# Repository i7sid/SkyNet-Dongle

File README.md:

SkyNet-Dongle
=============

Welcome to the SkyNet-Dongle git repository!
The initial work was done in the context of a bachelor thesis at the
Friedrich-Alexander University Erlangen-Nürnberg.
Some updates were made during a master thesis at the
Friedrich-Alexander University Erlangen-Nürnberg.

Hardware
--------
The main components are
* CPU: LPC1769
* Radio: [LoRa-Feather](https://learn.adafruit.com/adafruit-feather-m0-radio-with-lora-radio-module?view=all)

Firmware
--------
The firmware for the LPC1769 is written entirely in C99 and can **basically**
be compiled by a standard GNU GCC cross compiling toolchain.
Currently an Eclipse project is shipped that works with
[LPCXpresso](https://www.lpcware.com/lpcxpresso/download).
Additionally you need the [LPCOpen chip library](http://www.lpcware.com/lpcopen).

If both projects - lpc_chip_175x_6x and SkyNet-Dongle-Firmware - are present in
your current workspace you should be able to successfully compile the firmware.

The firmware uses the Si446x API library from Silicon Laboratories, Inc.
The library was slightly adjusted to compile for and work nicely on LPC1769.

Pinouts
-------
... are documented in `board/pinouts.txt`.

Flashing / Programming
----------------------
First flashing has to be done via ISP or JTAG.
Flash `bootloader/src/bootloader.bin` to the processor.
Afterwards you should be able to flash new firmware files
(.bin) via USB and mass storage emulation.

That works as following:
Send via USB CDC serial terminal a "goto bootloader" command.
You can use:

    ./usb-host/skynet-usb-host

(You have to compile the host application before that.)

The dongle restarts and goes into bootloader mode.
Now the dongle is detected by host as a mass storage device.
Copy firmware binary to the mass storage device and *eject the device* afterwards:

    sudo eject /dev/{devices name, usually sdb, sdc, sdd, or any...}

or:

    sudo umount {MOUNTPOINT}
    sudo udisk --detach /dev/{devices name, usually sdb, sdc, sdd, or any...}

Bootloader source: https://github.com/openxc/openlpc-USB_Bootloader

EAGLE files (schematics, layout)
--------------------------------

The eagle files contained in this repository
(schematics, layouts) use the following libraries:
* LPC1769: [lpc1xxx-v6.lbr](http://www.cadsoft.de/downloads/file/lpc1xxx-v6.lbr)
* HC-05: [Bluetooth HC-05.lbr](https://github.com/ErichStyger/mcuoneclipse/tree/master/Eagle/Library)
* MCP73871: [microchip-battery.lbr](https://github.com/scott-42/eagle-lib)
* Micro USB connector: [usb_con-update.lbr](http://www.cadsoft.de/downloads/file/usb_con-update.lbr)
* Switch: [switch-ck.lbr](https://github.com/robertstarr/lbr_user/blob/master/switch-ck.lbr)
* [Microbuilder Library](http://www.microbuilder.eu/Projects/EagleFootprintLibrary.aspx)
* RF4463PRO (from this repository)
* skynet_other (from this repository)

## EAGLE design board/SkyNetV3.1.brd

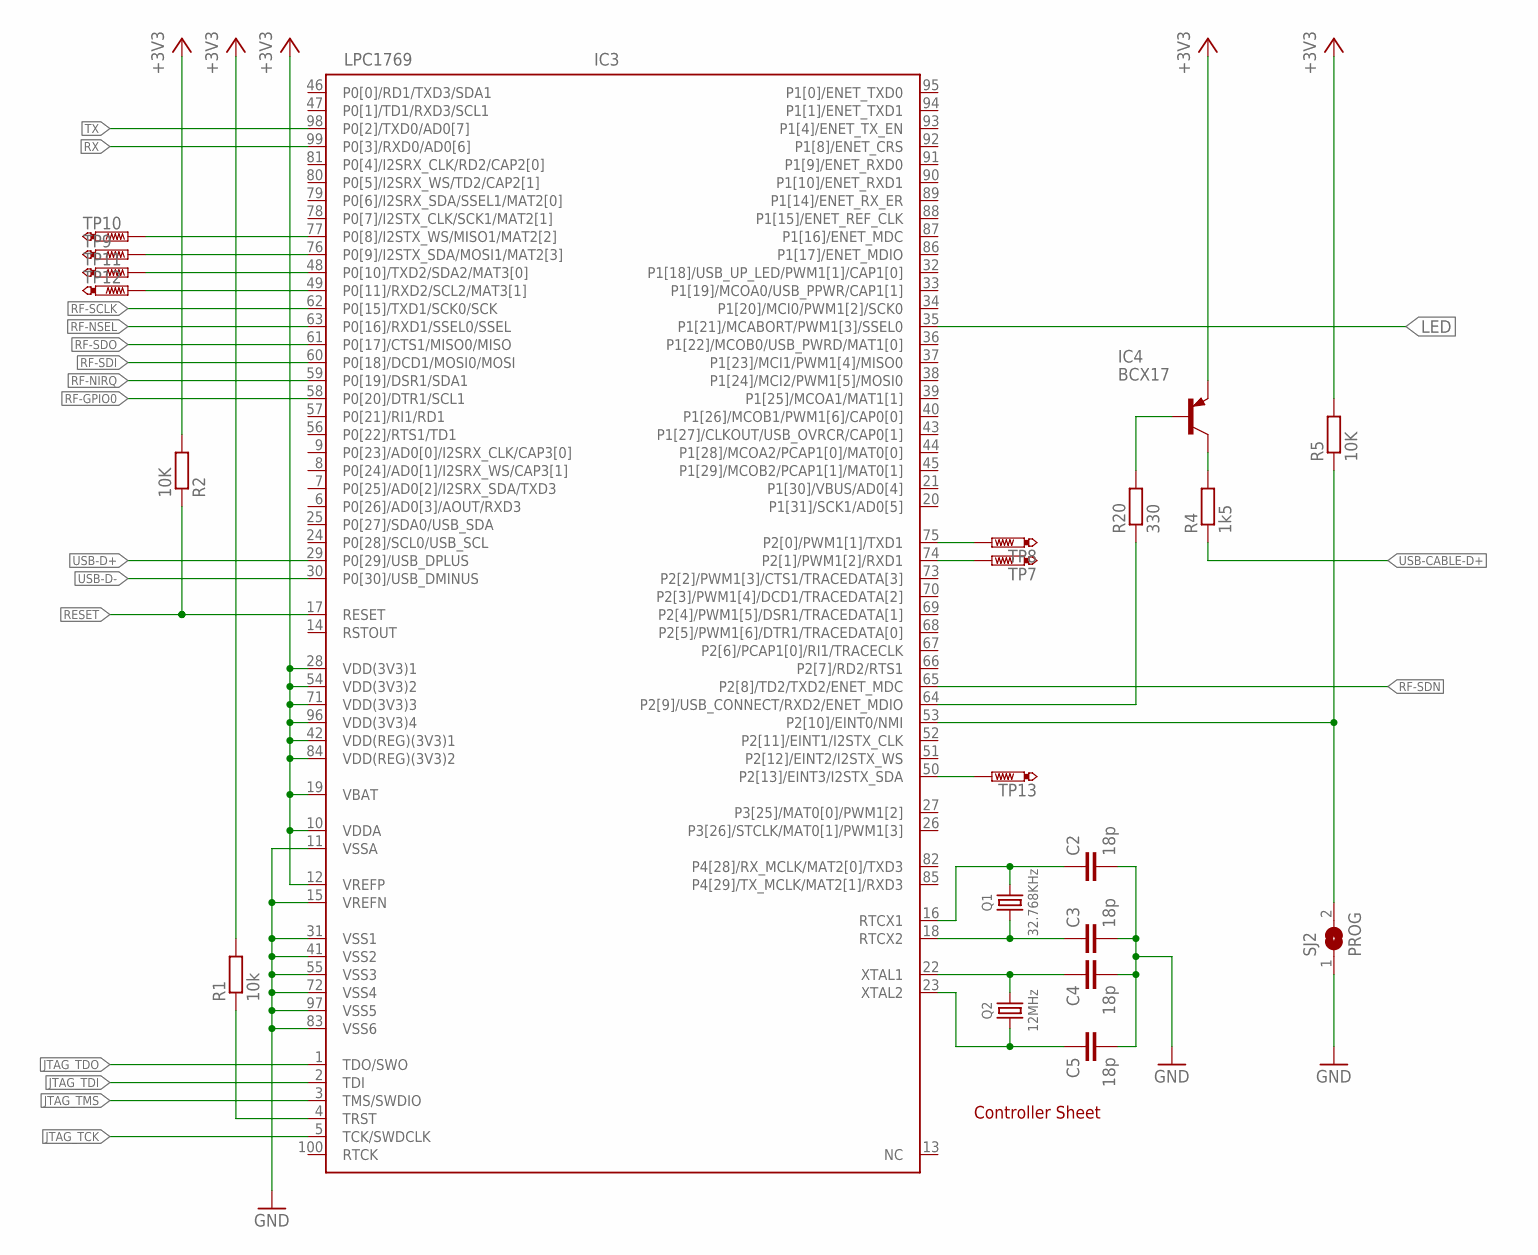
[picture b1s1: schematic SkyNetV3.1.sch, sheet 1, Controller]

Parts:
C2, C3, C4, C5: 18p; C0603
IC3: LPC1769; LQFP100-14X14
IC4: BCX17; SOT23
Q1: 32.768KHz; XTAL_49_18
Q2: 12MHz; XTAL_50_32
R1: 10k; R0603
R2, R5: 10K; R0603
R4: 1k5; R0603
R20: 330; R0603
SJ2: PROG; SJ
TP7, TP8, TP9, TP10, TP11, TP12, TP13: PTR1B1,27; B1,27

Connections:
+3V3: IC3.10 (VDDA), IC3.12 (VREFP), IC3.19 (VBAT), IC3.28 (VDD(3V3)1), IC3.42 (VDD(REG)(3V3)1), IC3.54 (VDD(3V3)2), IC3.71 (VDD(3V3)3), IC3.84 (VDD(REG)(3V3)2), IC3.96 (VDD(3V3)4), IC4.2 (E), R1.2, R2.2, R5.2; also elsewhere on the board
GND: C2.2, C3.2, C4.2, C5.2, IC3.11 (VSSA), IC3.15 (VREFN), IC3.31 (VSS1), IC3.41 (VSS2), IC3.55 (VSS3), IC3.72 (VSS4), IC3.83 (VSS6), IC3.97 (VSS5), SJ2.1; also elsewhere on the board
JTAG-TRST: IC3.4 (TRST), R1.1
JTAG_TCK: IC3.5 (TCK/SWDCLK); also elsewhere on the board
JTAG_TDI: IC3.2 (TDI); also elsewhere on the board
JTAG_TDO: IC3.1 (TDO/SWO); also elsewhere on the board
JTAG_TMS: IC3.3 (TMS/SWDIO); also elsewhere on the board
LED: IC3.35 (P1[21]/MCABORT/PWM1[3]/SSEL0); also elsewhere on the board
unnamed: IC3.75 (P2[0]/PWM1[1]/TXD1), TP8.TP
unnamed: IC3.76 (P0[9]/I2STX_SDA/MOSI1/MAT2[3]), TP9.TP
unnamed: IC3.77 (P0[8]/I2STX_WS/MISO1/MAT2[2]), TP10.TP
unnamed: IC3.74 (P2[1]/PWM1[2]/RXD1), TP7.TP
unnamed: IC3.49 (P0[11]/RXD2/SCL2/MAT3[1]), TP12.TP
unnamed: IC3.48 (P0[10]/TXD2/SDA2/MAT3[0]), TP11.TP
unnamed: IC3.50 (P2[13]/EINT3/I2STX_SDA), TP13.TP
PROG: IC3.53 (P2[10]/EINT0/NMI), R5.1, SJ2.2
RESET: IC3.17 (RESET), R2.1; also elsewhere on the board
RF-GPIO0: IC3.58 (P0[20]/DTR1/SCL1); also elsewhere on the board
RF-NIRQ: IC3.59 (P0[19]/DSR1/SDA1); also elsewhere on the board
RF-NSEL: IC3.63 (P0[16]/RXD1/SSEL0/SSEL); also elsewhere on the board
RF-SCLK: IC3.62 (P0[15]/TXD1/SCK0/SCK); also elsewhere on the board
RF-SDI: IC3.60 (P0[18]/DCD1/MOSI0/MOSI); also elsewhere on the board
RF-SDN: IC3.65 (P2[8]/TD2/TXD2/ENET_MDC); also elsewhere on the board
RF-SDO: IC3.61 (P0[17]/CTS1/MISO0/MISO); also elsewhere on the board
RTCX1: C2.1, IC3.16 (RTCX1), Q1.2
RTCX2: C3.1, IC3.18 (RTCX2), Q1.1
RX: IC3.99 (P0[3]/RXD0/AD0[6]); also elsewhere on the board
TX: IC3.98 (P0[2]/TXD0/AD0[7]); also elsewhere on the board
USB-CABLE-D+: R4.1; also elsewhere on the board
USB-CON: IC3.64 (P2[9]/USB_CONNECT/RXD2/ENET_MDIO), R20.1
USB-CON-TRANS: IC4.1 (B), R20.2
USB-CON-TRANS-2: IC4.3 (C), R4.2
USB-D+: IC3.29 (P0[29]/USB_DPLUS); also elsewhere on the board
USB-D-: IC3.30 (P0[30]/USB_DMINUS); also elsewhere on the board
XTAL1: C4.1, IC3.22 (XTAL1), Q2.3 (2)
XTAL2: C5.1, IC3.23 (XTAL2), Q2.1

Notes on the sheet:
Controller Sheet

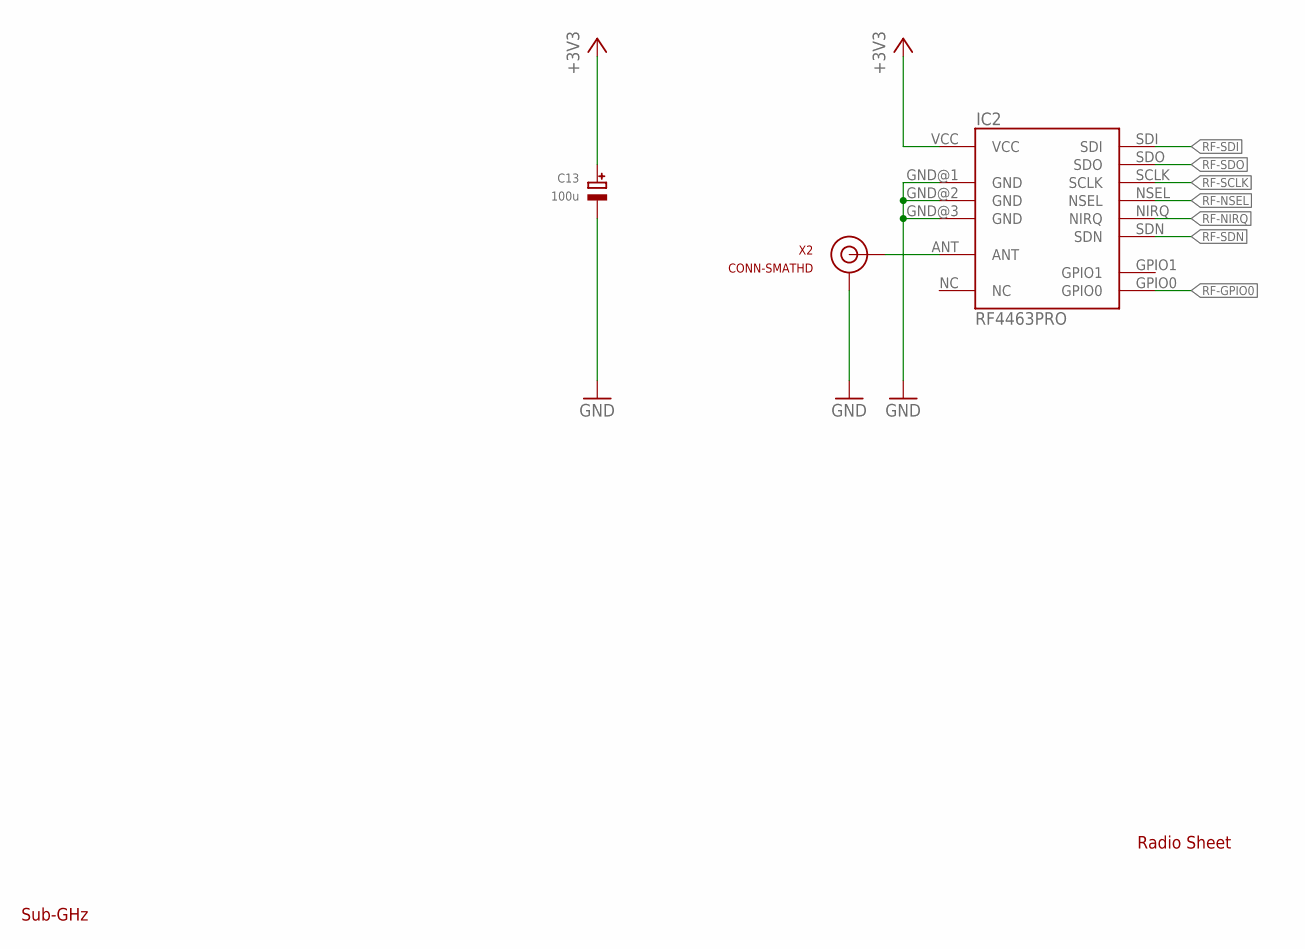
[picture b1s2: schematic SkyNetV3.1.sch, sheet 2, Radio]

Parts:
C13: 100u; EIA6032-28/C-W
IC2: RF4463PRO; STD_BOARD
X2: CONN-SMATHD; SMA-THD

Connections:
+3V3: C13.+, IC2.VCC; also elsewhere on the board
ANT: IC2.ANT, X2.SIG (SIGNAL)
GND: C13.-, IC2.GND@1 (GND), IC2.GND@2 (GND), IC2.GND@3 (GND), X2.GND@0 (GND), X2.GND@1 (GND), X2.GND@2 (GND), X2.GND@3 (GND); also elsewhere on the board
RF-GPIO0: IC2.GPIO0; also elsewhere on the board
RF-NIRQ: IC2.NIRQ; also elsewhere on the board
RF-NSEL: IC2.NSEL; also elsewhere on the board
RF-SCLK: IC2.SCLK; also elsewhere on the board
RF-SDI: IC2.SDI; also elsewhere on the board
RF-SDN: IC2.SDN; also elsewhere on the board
RF-SDO: IC2.SDO; also elsewhere on the board

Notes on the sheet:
Radio Sheet
Sub-GHz

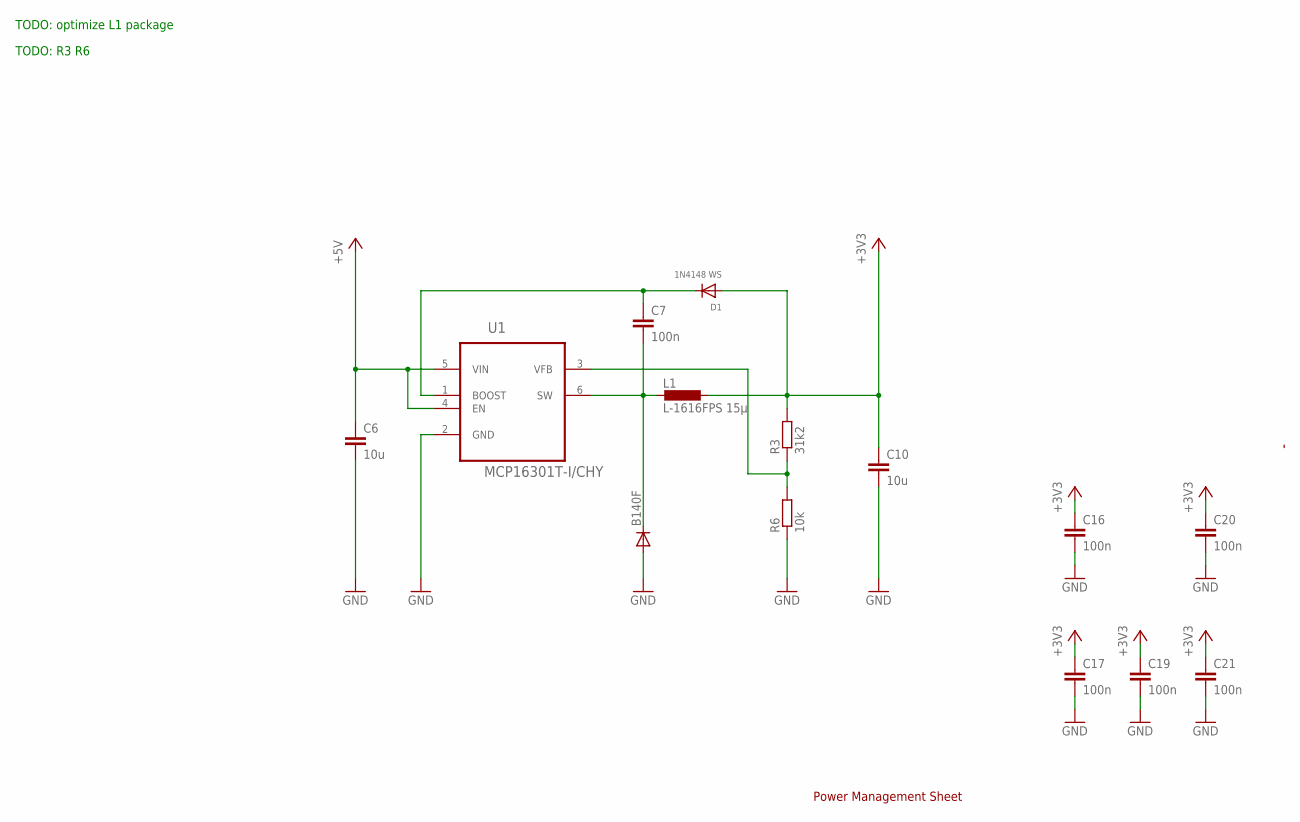
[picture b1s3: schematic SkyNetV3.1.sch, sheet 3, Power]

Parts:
B140F: DIODE-DO214AC; DO214AC
C6, C10: 10u; C0805
C7, C16, C17, C19, C20, C21: 100n; C0603
D1: 1N4148 WS; SOD-323
L1: L-1616FPS 15µ; LQH55D
R3: 31k2; R0603
R6: 10k; R0603
U1: MCP16301T-I/CHY; SOT95P290X145-6N

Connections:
+3V3: C10.1, C16.1, C17.1, C19.1, C20.1, C21.1, D1.A, L1.P$1 (1), R3.2; also elsewhere on the board
+5V: C6.1, U1.4 (EN), U1.5 (VIN); also elsewhere on the board
GND: B140F.A, C6.2, C10.2, C16.2, C17.2, C19.2, C20.2, C21.2, R6.1, U1.2 (GND); also elsewhere on the board
unnamed: B140F.C, C7.2, L1.P$2 (2), U1.6 (SW)
unnamed: C7.1, D1.C, U1.1 (BOOST)
unnamed: R3.1, R6.2, U1.3 (VFB)

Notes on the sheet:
Power Management Sheet
TODO: optimize L1 package
TODO: R3 R6

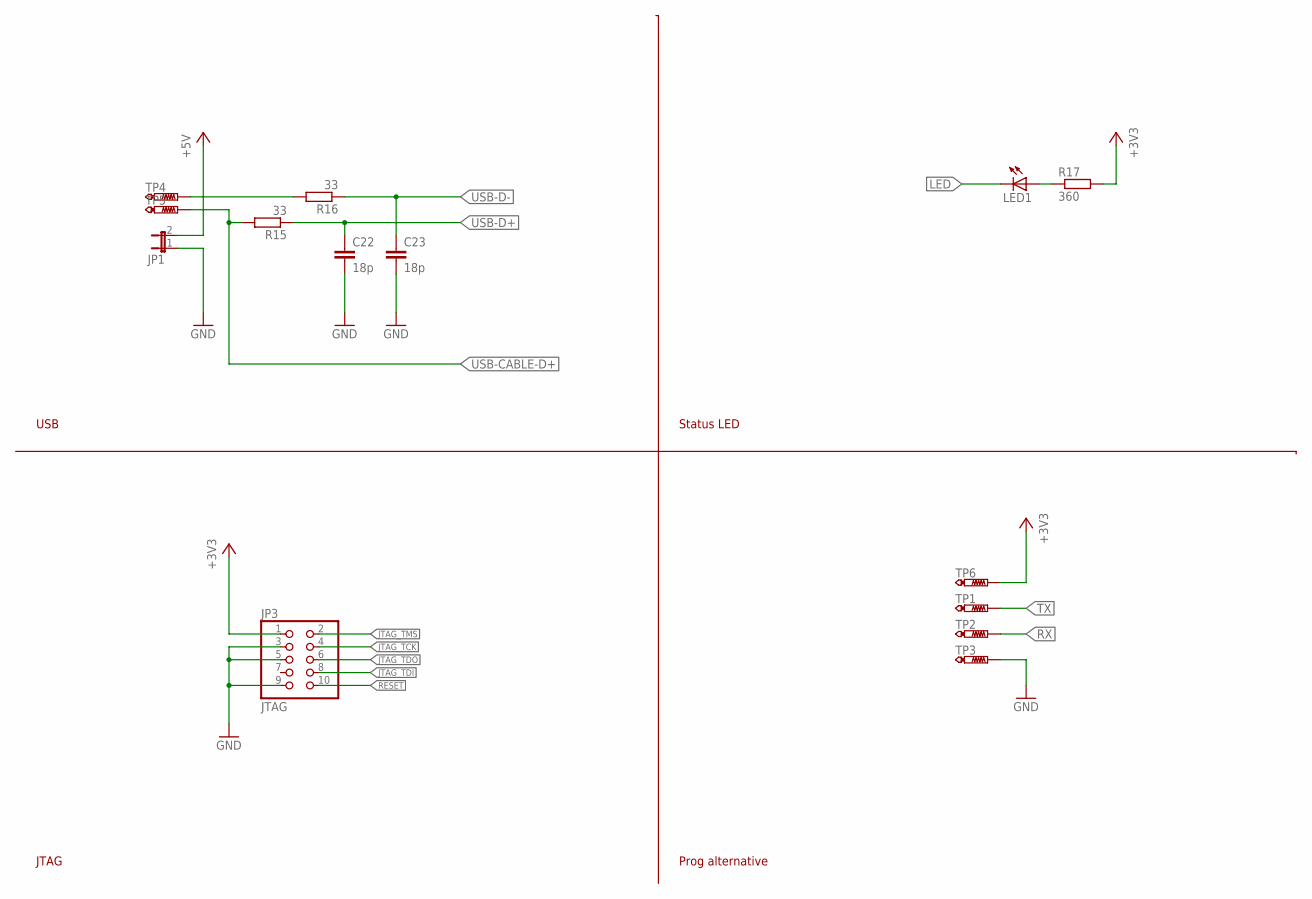
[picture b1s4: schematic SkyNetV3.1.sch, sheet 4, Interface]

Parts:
C22, C23: 18p; C0603
JP1: JP1E; JP1
JP3: JTAG; 2X05_1.27MM_SMT
LED1: LEDCHIP-LED0805; CHIP-LED0805
R15, R16: 33; R0603
R17: 360; R0603
TP1, TP2, TP4, TP5: PTR1B1,27; B1,27
TP3, TP6: PTR1B2,54; B2,54

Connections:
+3V3: JP3.1, R17.2, TP6.TP; also elsewhere on the board
+5V: JP1.2; also elsewhere on the board
GND: C22.2, C23.2, JP1.1, JP3.3, JP3.5, JP3.9, TP3.TP; also elsewhere on the board
JTAG_TCK: JP3.4; also elsewhere on the board
JTAG_TDI: JP3.8; also elsewhere on the board
JTAG_TDO: JP3.6; also elsewhere on the board
JTAG_TMS: JP3.2; also elsewhere on the board
LED: LED1.C; also elsewhere on the board
LED-R-R: LED1.A, R17.1
RESET: JP3.10; also elsewhere on the board
RX: TP2.TP; also elsewhere on the board
TX: TP1.TP; also elsewhere on the board
USB-CABLE-D+: R15.2, TP5.TP; also elsewhere on the board
USB-CABLE-D-: R16.2, TP4.TP
USB-D+: C22.1, R15.1; also elsewhere on the board
USB-D-: C23.1, R16.1; also elsewhere on the board

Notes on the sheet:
USB
Status LED
Prog alternative
JTAG

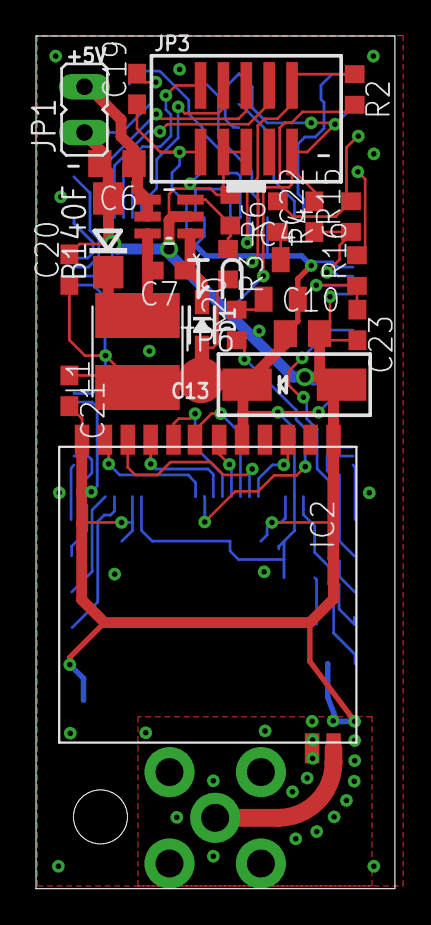
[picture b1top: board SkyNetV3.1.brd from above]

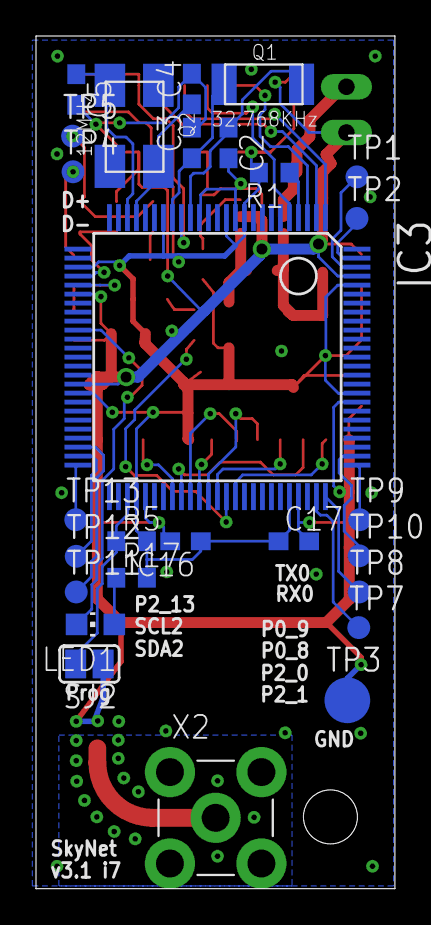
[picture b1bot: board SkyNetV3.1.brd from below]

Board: 2 copper layers, 19.9 x 47.4 mm, 52 parts (27 on the bottom side), 43 nets.

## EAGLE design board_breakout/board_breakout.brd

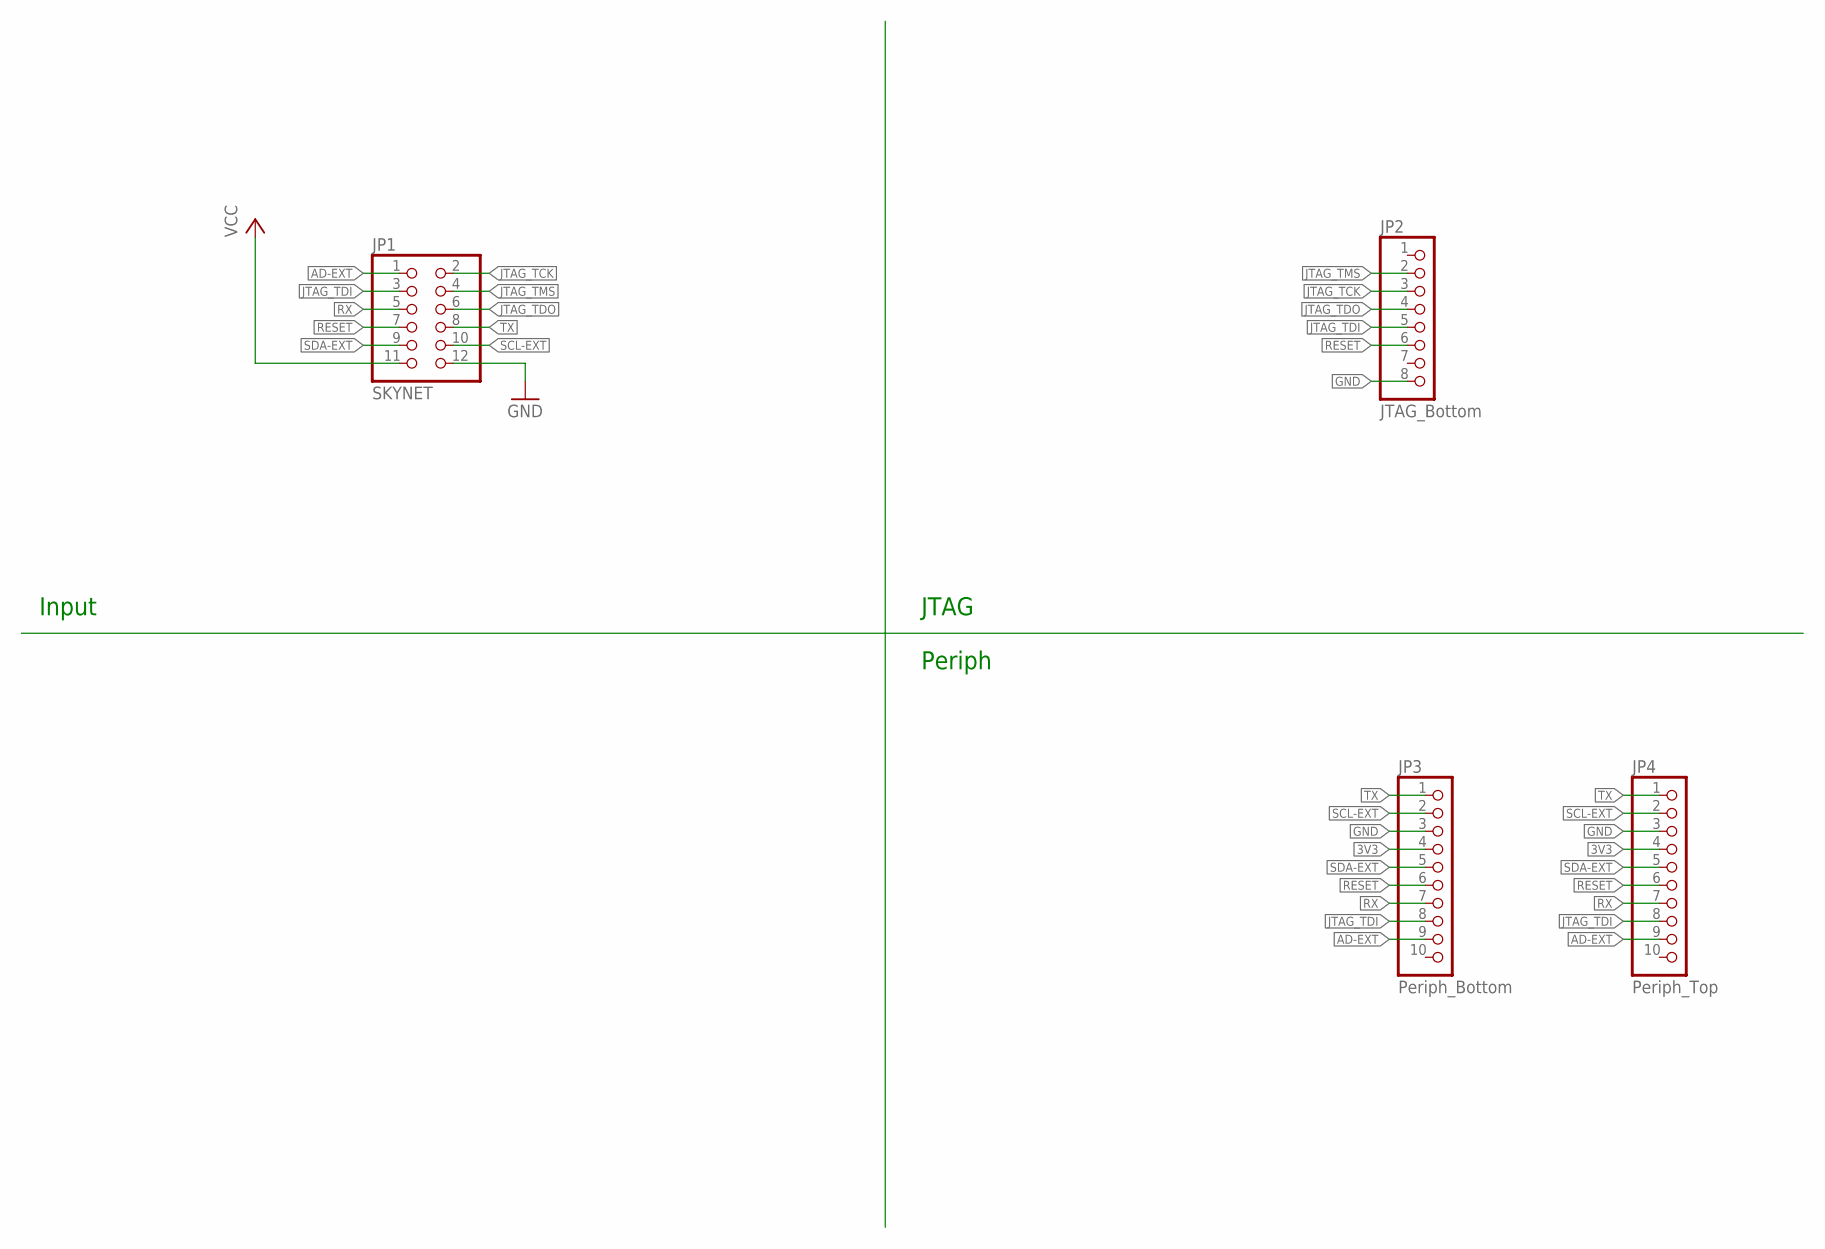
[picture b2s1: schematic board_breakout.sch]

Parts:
JP1: SKYNET; 2X06M
JP2: JTAG_Bottom; 1X08
JP3: Periph_Bottom; 1X10
JP4: Periph_Top; 1X10_SMT

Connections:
3V3: JP1.11, JP3.4, JP4.4
AD-EXT: JP1.1, JP3.9, JP4.9
GND: JP1.12, JP2.8, JP3.3, JP4.3
JTAG_TCK: JP1.2, JP2.3
JTAG_TDI: JP1.3, JP2.5, JP3.8, JP4.8
JTAG_TDO: JP1.6, JP2.4
JTAG_TMS: JP1.4, JP2.2
RESET: JP1.7, JP2.6, JP3.6, JP4.6
RX: JP1.5, JP3.7, JP4.7
SCL-EXT: JP1.10, JP3.2, JP4.2
SDA-EXT: JP1.9, JP3.5, JP4.5
TX: JP1.8, JP3.1, JP4.1

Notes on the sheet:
Input
JTAG
Periph

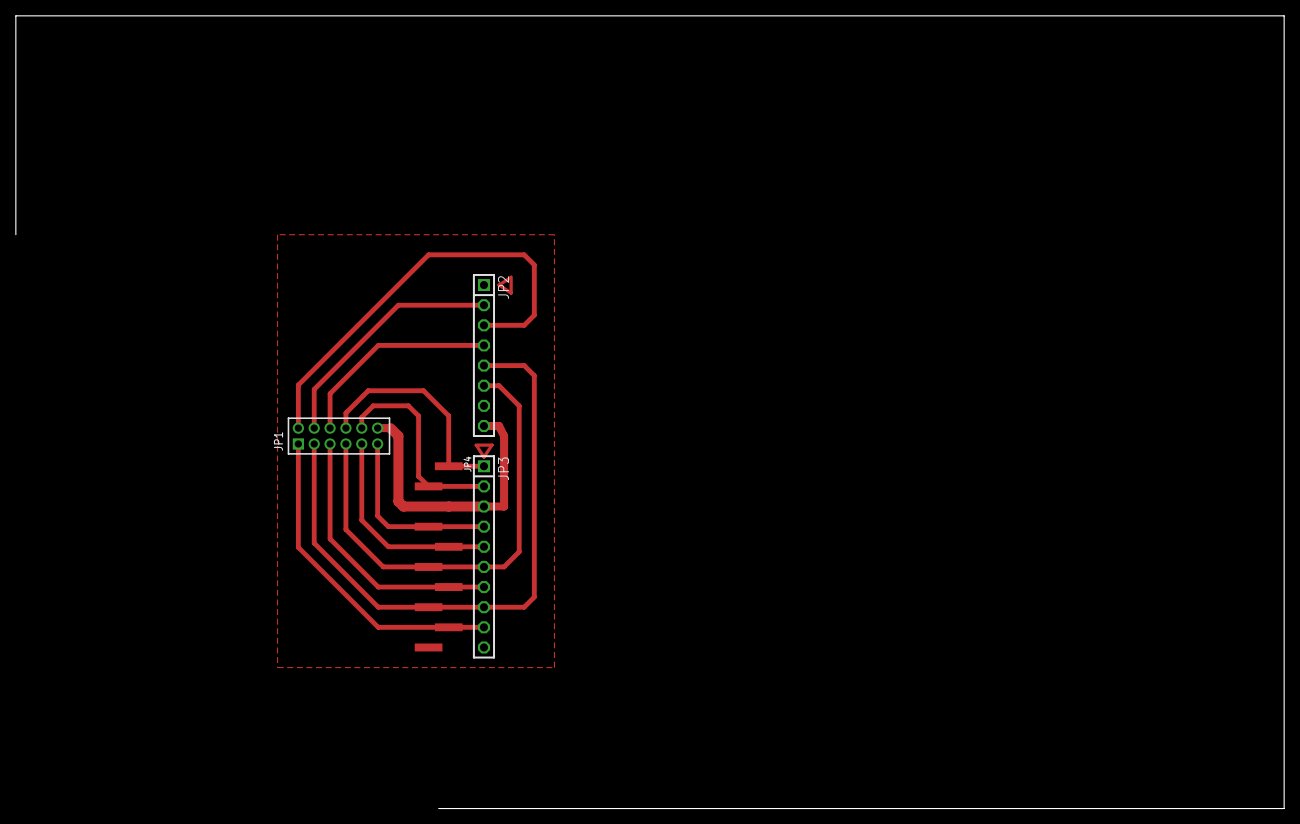
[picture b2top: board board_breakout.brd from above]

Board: 2 copper layers, 4 parts (0 on the bottom side), 12 nets.

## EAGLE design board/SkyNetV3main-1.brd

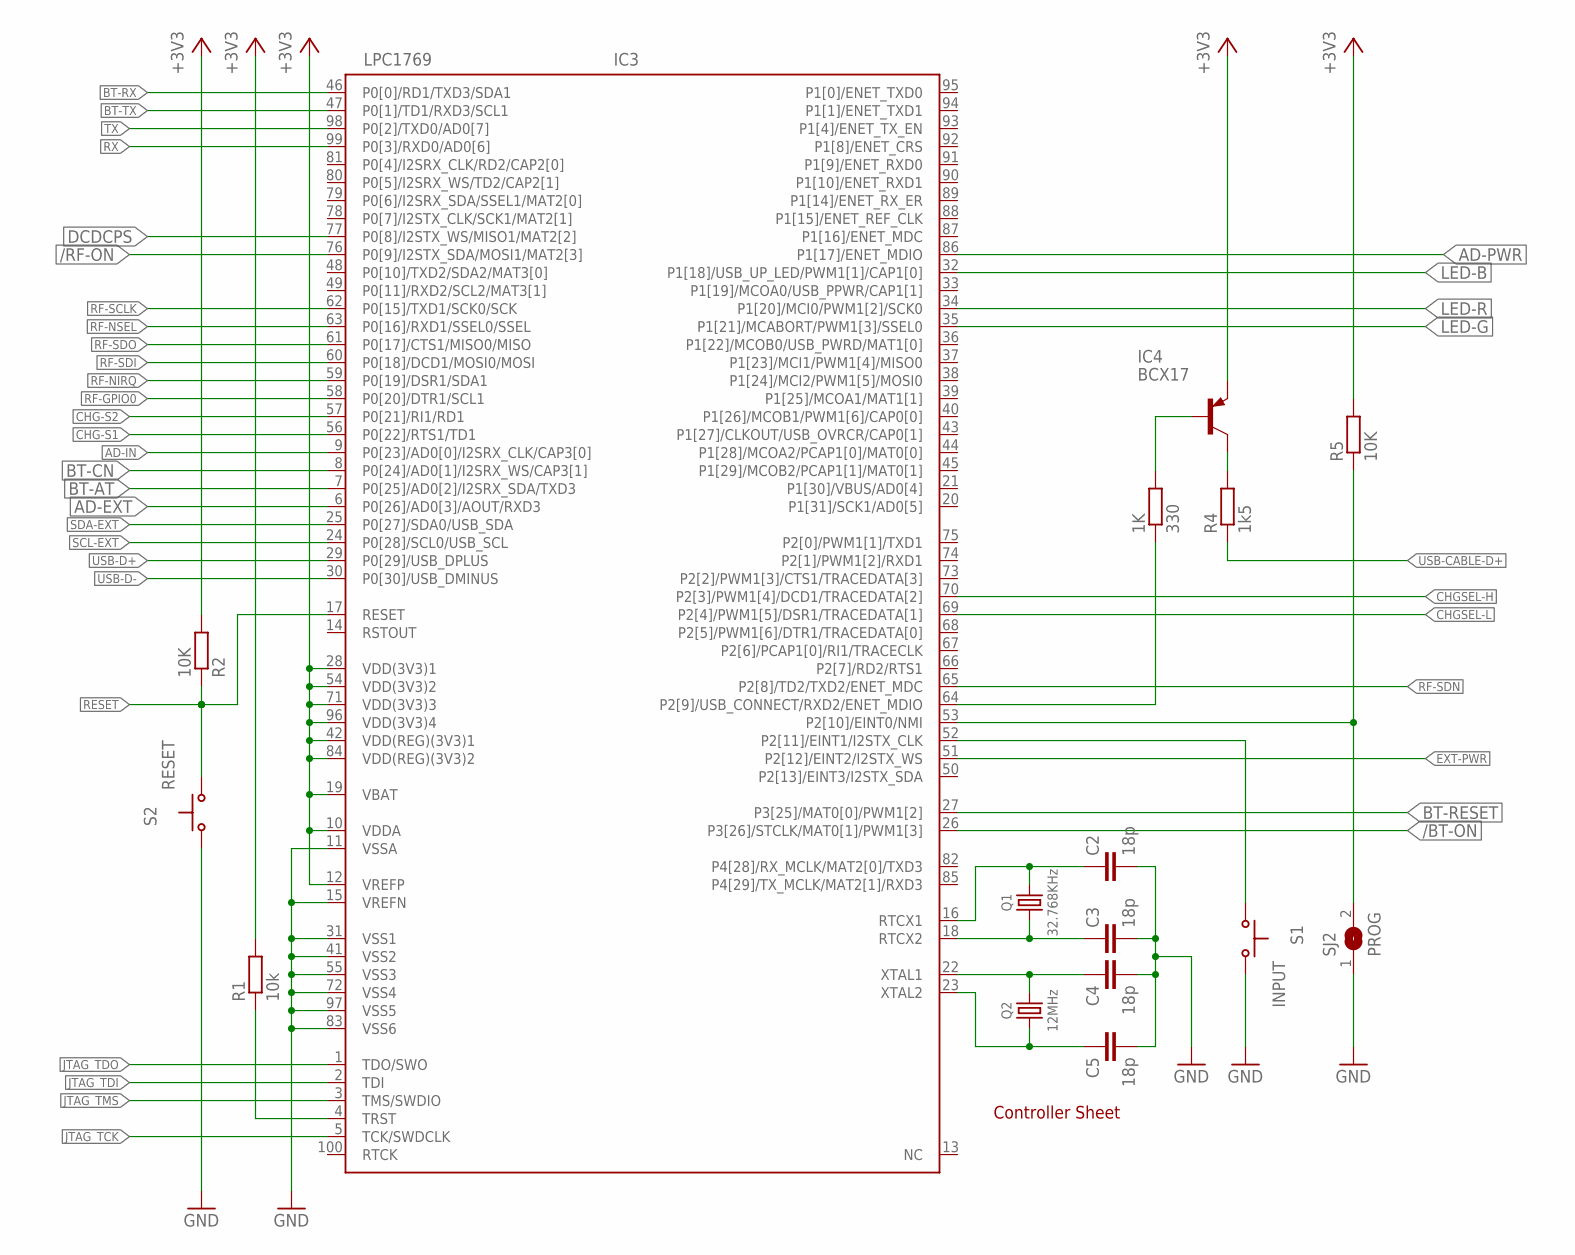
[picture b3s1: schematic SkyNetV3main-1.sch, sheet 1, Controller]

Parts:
1K: 330; R0603
C2, C3, C4, C5: 18p; C0603
IC3: LPC1769; LQFP100-14X14
IC4: BCX17; SOT23
Q1: 32.768KHz; XTAL_49_18
Q2: 12MHz; XTAL_50_32
R1: 10k; R0603
R2, R5: 10K; R0603
R4: 1k5; R0603
S1: INPUT; PTS645-SMD
S2: RESET; PTS645-SMD
SJ2: PROG; SJ

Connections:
+3V3: IC3.10 (VDDA), IC3.12 (VREFP), IC3.19 (VBAT), IC3.28 (VDD(3V3)1), IC3.42 (VDD(REG)(3V3)1), IC3.54 (VDD(3V3)2), IC3.71 (VDD(3V3)3), IC3.84 (VDD(REG)(3V3)2), IC3.96 (VDD(3V3)4), IC4.2 (E), R1.2, R2.2, R5.2; also elsewhere on the board
/BT-ON: IC3.26 (P3[26]/STCLK/MAT0[1]/PWM1[3]); also elsewhere on the board
/RF-ON: IC3.76 (P0[9]/I2STX_SDA/MOSI1/MAT2[3]); also elsewhere on the board
AD-EXT: IC3.6 (P0[26]/AD0[3]/AOUT/RXD3); also elsewhere on the board
AD-IN: IC3.9 (P0[23]/AD0[0]/I2SRX_CLK/CAP3[0]); also elsewhere on the board
AD-PWR: IC3.86 (P1[17]/ENET_MDIO); also elsewhere on the board
BT-AT: IC3.7 (P0[25]/AD0[2]/I2SRX_SDA/TXD3); also elsewhere on the board
BT-CN: IC3.8 (P0[24]/AD0[1]/I2SRX_WS/CAP3[1]); also elsewhere on the board
BT-RESET: IC3.27 (P3[25]/MAT0[0]/PWM1[2]); also elsewhere on the board
BT-RX: IC3.46 (P0[0]/RD1/TXD3/SDA1); also elsewhere on the board
BT-TX: IC3.47 (P0[1]/TD1/RXD3/SCL1); also elsewhere on the board
CHG-S1: IC3.56 (P0[22]/RTS1/TD1); also elsewhere on the board
CHG-S2: IC3.57 (P0[21]/RI1/RD1); also elsewhere on the board
CHGSEL-H: IC3.70 (P2[3]/PWM1[4]/DCD1/TRACEDATA[2]); also elsewhere on the board
CHGSEL-L: IC3.69 (P2[4]/PWM1[5]/DSR1/TRACEDATA[1]); also elsewhere on the board
DCDCPS: IC3.77 (P0[8]/I2STX_WS/MISO1/MAT2[2]); also elsewhere on the board
EXT-PWR: IC3.51 (P2[12]/EINT2/I2STX_WS); also elsewhere on the board
GND: C2.2, C3.2, C4.2, C5.2, IC3.11 (VSSA), IC3.15 (VREFN), IC3.31 (VSS1), IC3.41 (VSS2), IC3.55 (VSS3), IC3.72 (VSS4), IC3.83 (VSS6), IC3.97 (VSS5), S1.3 (S), S1.4 (S), S2.1, S2.2, SJ2.1; also elsewhere on the board
INPUT: IC3.52 (P2[11]/EINT1/I2STX_CLK), S1.1, S1.2
JTAG-TRST: IC3.4 (TRST), R1.1
JTAG_TCK: IC3.5 (TCK/SWDCLK); also elsewhere on the board
JTAG_TDI: IC3.2 (TDI); also elsewhere on the board
JTAG_TDO: IC3.1 (TDO/SWO); also elsewhere on the board
JTAG_TMS: IC3.3 (TMS/SWDIO); also elsewhere on the board
LED-B: IC3.32 (P1[18]/USB_UP_LED/PWM1[1]/CAP1[0]); also elsewhere on the board
LED-G: IC3.35 (P1[21]/MCABORT/PWM1[3]/SSEL0); also elsewhere on the board
LED-R: IC3.34 (P1[20]/MCI0/PWM1[2]/SCK0); also elsewhere on the board
PROG: IC3.53 (P2[10]/EINT0/NMI), R5.1, SJ2.2
RESET: IC3.17 (RESET), R2.1, S2.3 (S), S2.4 (S); also elsewhere on the board
RF-GPIO0: IC3.58 (P0[20]/DTR1/SCL1); also elsewhere on the board
RF-NIRQ: IC3.59 (P0[19]/DSR1/SDA1); also elsewhere on the board
RF-NSEL: IC3.63 (P0[16]/RXD1/SSEL0/SSEL); also elsewhere on the board
RF-SCLK: IC3.62 (P0[15]/TXD1/SCK0/SCK); also elsewhere on the board
RF-SDI: IC3.60 (P0[18]/DCD1/MOSI0/MOSI); also elsewhere on the board
RF-SDN: IC3.65 (P2[8]/TD2/TXD2/ENET_MDC); also elsewhere on the board
RF-SDO: IC3.61 (P0[17]/CTS1/MISO0/MISO); also elsewhere on the board
RTCX1: C2.1, IC3.16 (RTCX1), Q1.2
RTCX2: C3.1, IC3.18 (RTCX2), Q1.1
RX: IC3.99 (P0[3]/RXD0/AD0[6]); also elsewhere on the board
SCL-EXT: IC3.24 (P0[28]/SCL0/USB_SCL); also elsewhere on the board
SDA-EXT: IC3.25 (P0[27]/SDA0/USB_SDA); also elsewhere on the board
TX: IC3.98 (P0[2]/TXD0/AD0[7]); also elsewhere on the board
USB-CABLE-D+: R4.1; also elsewhere on the board
USB-CON: 1K.1, IC3.64 (P2[9]/USB_CONNECT/RXD2/ENET_MDIO)
USB-CON-TRANS: 1K.2, IC4.1 (B)
USB-CON-TRANS-2: IC4.3 (C), R4.2
USB-D+: IC3.29 (P0[29]/USB_DPLUS); also elsewhere on the board
USB-D-: IC3.30 (P0[30]/USB_DMINUS); also elsewhere on the board
XTAL1: C4.1, IC3.22 (XTAL1), Q2.3 (2)
XTAL2: C5.1, IC3.23 (XTAL2), Q2.1

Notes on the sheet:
Controller Sheet

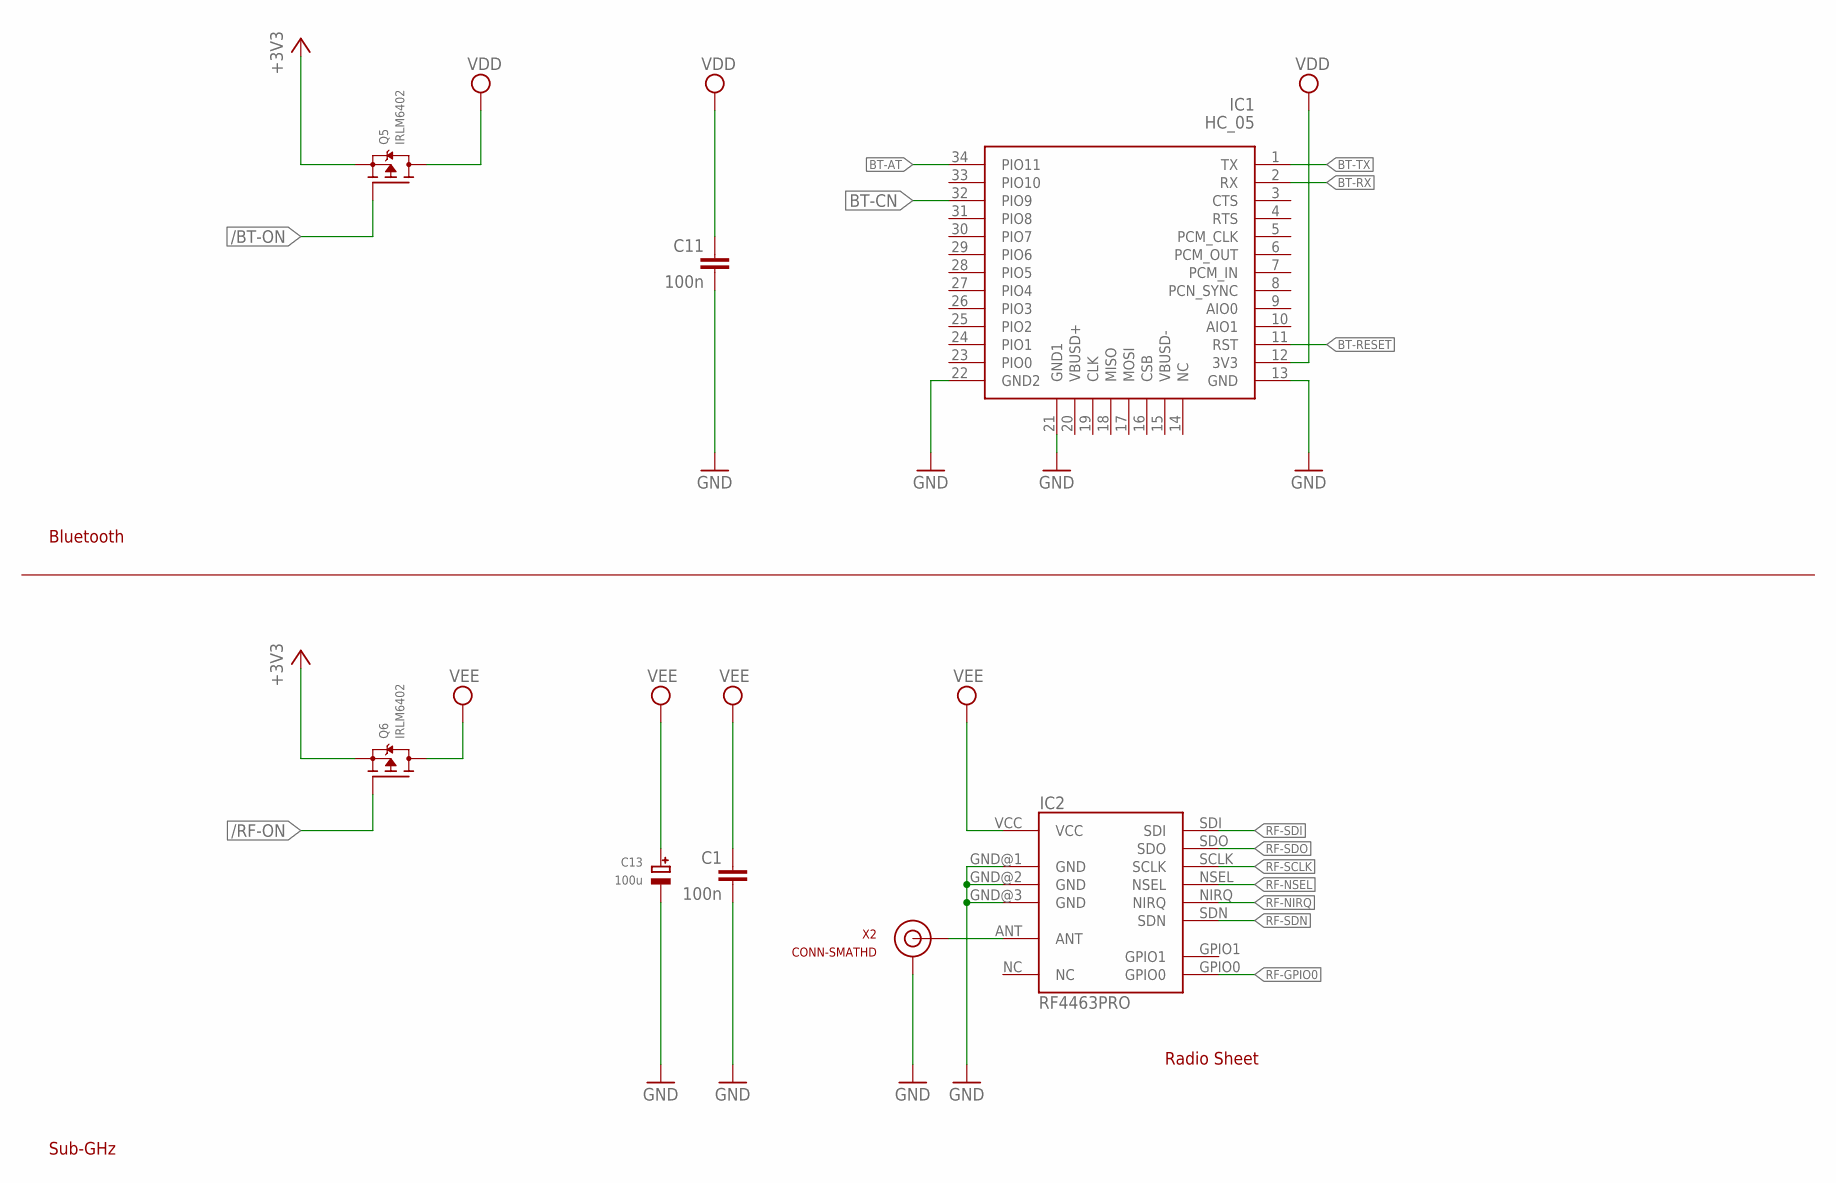
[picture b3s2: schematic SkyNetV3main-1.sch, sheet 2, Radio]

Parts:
C1, C11: 100n; C1206K
C13: 100u; EIA6032-28/C-W
IC1: HC_05; BLUETOOTH_SMD
IC2: RF4463PRO; STD_BOARD
Q5, Q6: IRLM6402; SOT23-WIDE
X2: CONN-SMATHD; SMA-THD

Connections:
+3V3: Q5.2 (S), Q6.2 (S); also elsewhere on the board
/BT-ON: Q5.1 (G); also elsewhere on the board
/RF-ON: Q6.1 (G); also elsewhere on the board
ANT: IC2.ANT, X2.SIG (SIGNAL)
BT-AT: IC1.34 (PIO11); also elsewhere on the board
BT-CN: IC1.32 (PIO9); also elsewhere on the board
BT-RESET: IC1.11 (RST); also elsewhere on the board
BT-RX: IC1.2 (RX); also elsewhere on the board
BT-TX: IC1.1 (TX); also elsewhere on the board
GND: C1.2, C11.2, C13.-, IC1.13 (GND), IC1.21 (GND1), IC1.22 (GND2), IC2.GND@1 (GND), IC2.GND@2 (GND), IC2.GND@3 (GND), X2.GND@0 (GND), X2.GND@1 (GND), X2.GND@2 (GND), X2.GND@3 (GND); also elsewhere on the board
RF-GPIO0: IC2.GPIO0; also elsewhere on the board
RF-NIRQ: IC2.NIRQ; also elsewhere on the board
RF-NSEL: IC2.NSEL; also elsewhere on the board
RF-SCLK: IC2.SCLK; also elsewhere on the board
RF-SDI: IC2.SDI; also elsewhere on the board
RF-SDN: IC2.SDN; also elsewhere on the board
RF-SDO: IC2.SDO; also elsewhere on the board
VDD: C11.1, IC1.12 (3V3), Q5.3 (D)
VEE: C1.1, C13.+, IC2.VCC, Q6.3 (D)

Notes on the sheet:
Radio Sheet
Bluetooth
Sub-GHz

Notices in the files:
parts and their libraries:
microbuilder: This work is placed in the public domain, and may be freely used for commercial and non-commercial work with the following conditions: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
switch-ck: Copyright (C) 2011, Bob Starr
